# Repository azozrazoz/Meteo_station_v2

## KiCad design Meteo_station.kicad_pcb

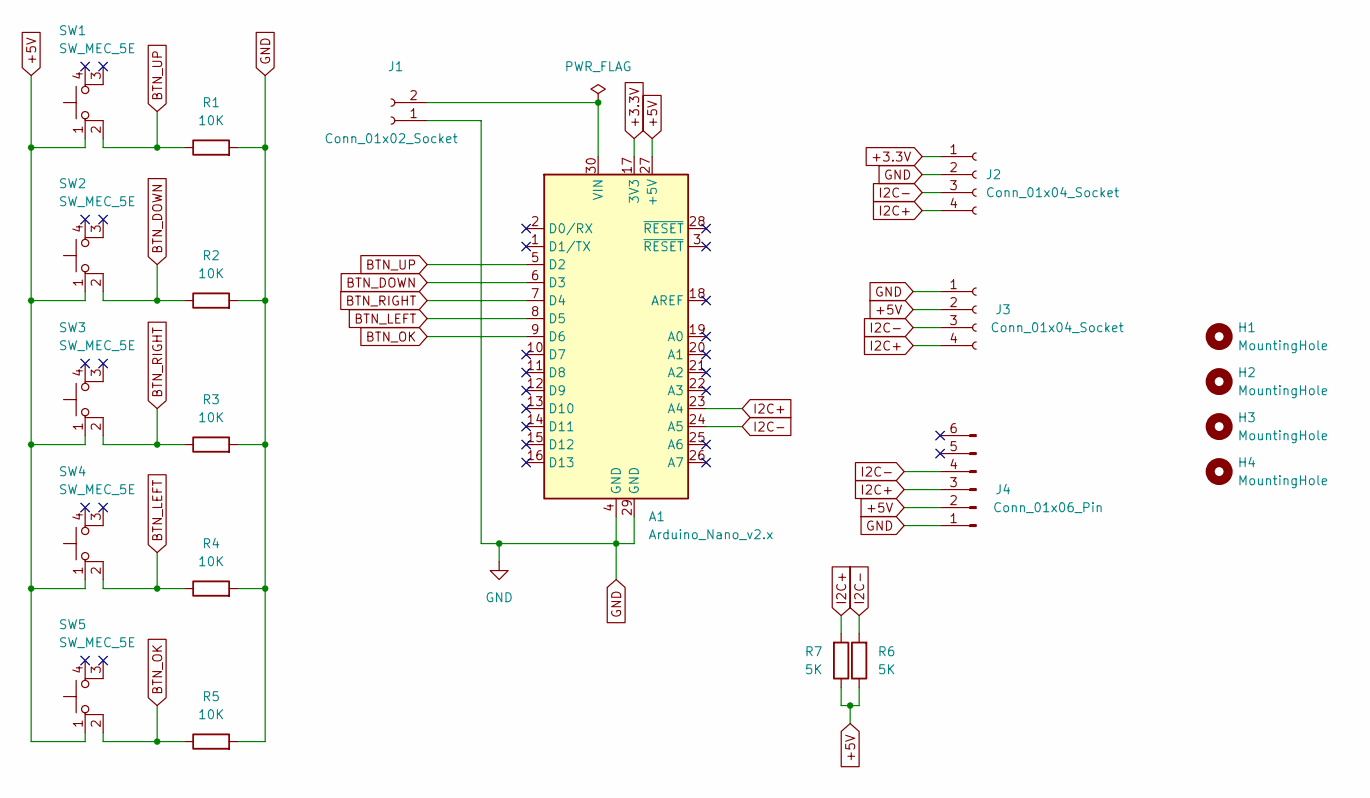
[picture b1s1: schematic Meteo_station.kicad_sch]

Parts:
A1: Arduino_Nano_v2.x; Arduino_Nano
H1, H2, H3, H4: MountingHole; MountingHole_2.5mm
J1: Conn_01x02_Socket; PinHeader_1x02_P2.54mm_Vertical
J2, J3: Conn_01x04_Socket; PinHeader_1x04_P2.54mm_Vertical
J4: Conn_01x06_Pin; PinHeader_1x06_P2.54mm_Vertical
R1, R2, R3, R4, R5: 10K; R_Axial_DIN0309_L9.0mm_D3.2mm_P15.24mm_Horizontal
R6, R7: 5K; R_0805_2012Metric
SW1, SW2, SW3, SW4, SW5: SW_MEC_5E; SW_PUSH_6mm_H5mm

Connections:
+3.3V: A1.17 (3V3), J2.1
+5V: A1.27 (+5V), J3.2, J4.2, R6.1, R7.1, SW1.1, SW2.1, SW3.1, SW4.1, SW5.1
BTN_DOWN: A1.6 (D3), R2.1, SW2.2
BTN_LEFT: A1.8 (D5), R4.1, SW4.2
BTN_OK: A1.9 (D6), R5.1, SW5.2
BTN_RIGHT: A1.7 (D4), R3.1, SW3.2
BTN_UP: A1.5 (D2), R1.1, SW1.2
GND: A1.4 (GND), A1.29 (GND), J1.1, J2.2, J3.1, J4.1, R1.2, R2.2, R3.2, R4.2, R5.2
I2C+: A1.23 (A4), J2.4, J3.4, J4.3, R7.2
I2C-: A1.24 (A5), J2.3, J3.3, J4.4, R6.2
unnamed: A1.30 (VIN), J1.2

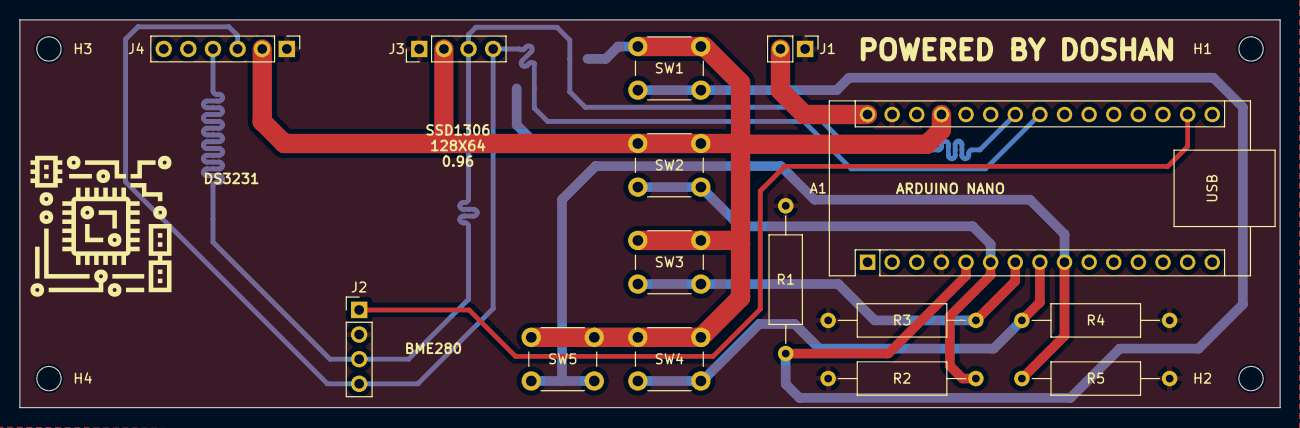
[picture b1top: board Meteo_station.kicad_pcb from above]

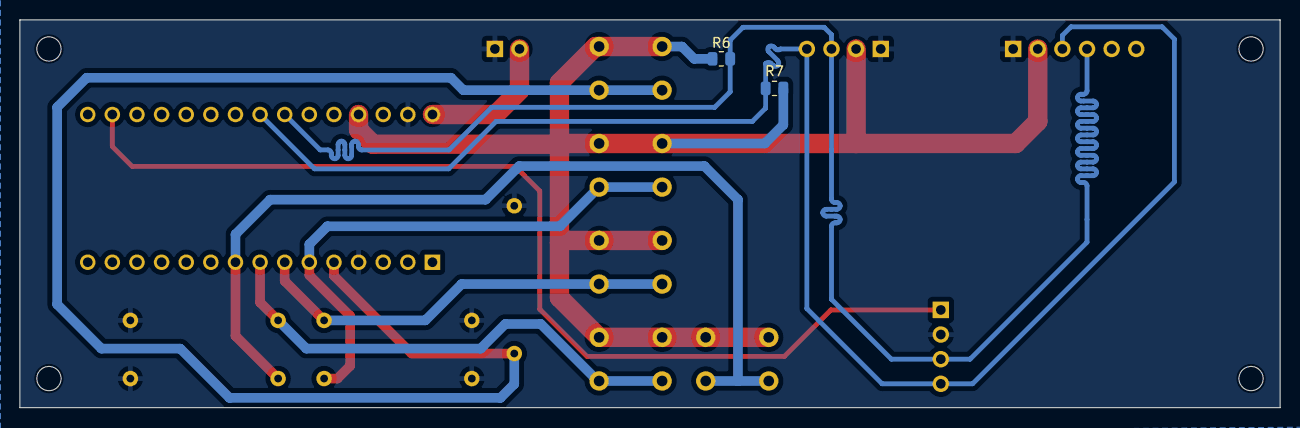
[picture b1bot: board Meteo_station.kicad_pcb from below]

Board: 2 copper layers, 130.0 x 40.0 mm, 21 parts (2 on the bottom side), 11 nets.

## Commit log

2024-01-19 some fix
